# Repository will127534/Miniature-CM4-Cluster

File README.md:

# Miniature CM4 Cluster
A dense Cluster for four Raspberry Pi 4 Compute Module 4

Here is the main description: [https://will127534.github.io/Miniature-CM4-Cluster/](https://will127534.github.io/Miniature-CM4-Cluster/)

## System Arch

## Files
* ClusterHat - PCB files for CLuster Hat
* CM4Card - PCB files for CM4 Card
* Software - Code for Raspberry Pi Pico & I2C EEPROM image for USB Hub
* Mechanical - STL for the dual 4cm fan frame 

## Notes
* RTL8367N Datasheet comes from here https://github.com/libc0607/Realtek_switch_hacking
* Designed with KiCad 5.99.0-12597-g9f841da98e

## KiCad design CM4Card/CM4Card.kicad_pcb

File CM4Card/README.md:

# CM4 Card
The PCB board files for the CM4 Card

## Notes
* Because the interconnector is using M.2, the board thickness is limited to 0.8mm
* Yes, I did put most of the components under CM4. The SD card slot is 1.45mm in height. It is fine with the 3mm connector height for the CM4.
* The address for TMP117 is depend on the Cluster Hat.

## Preview

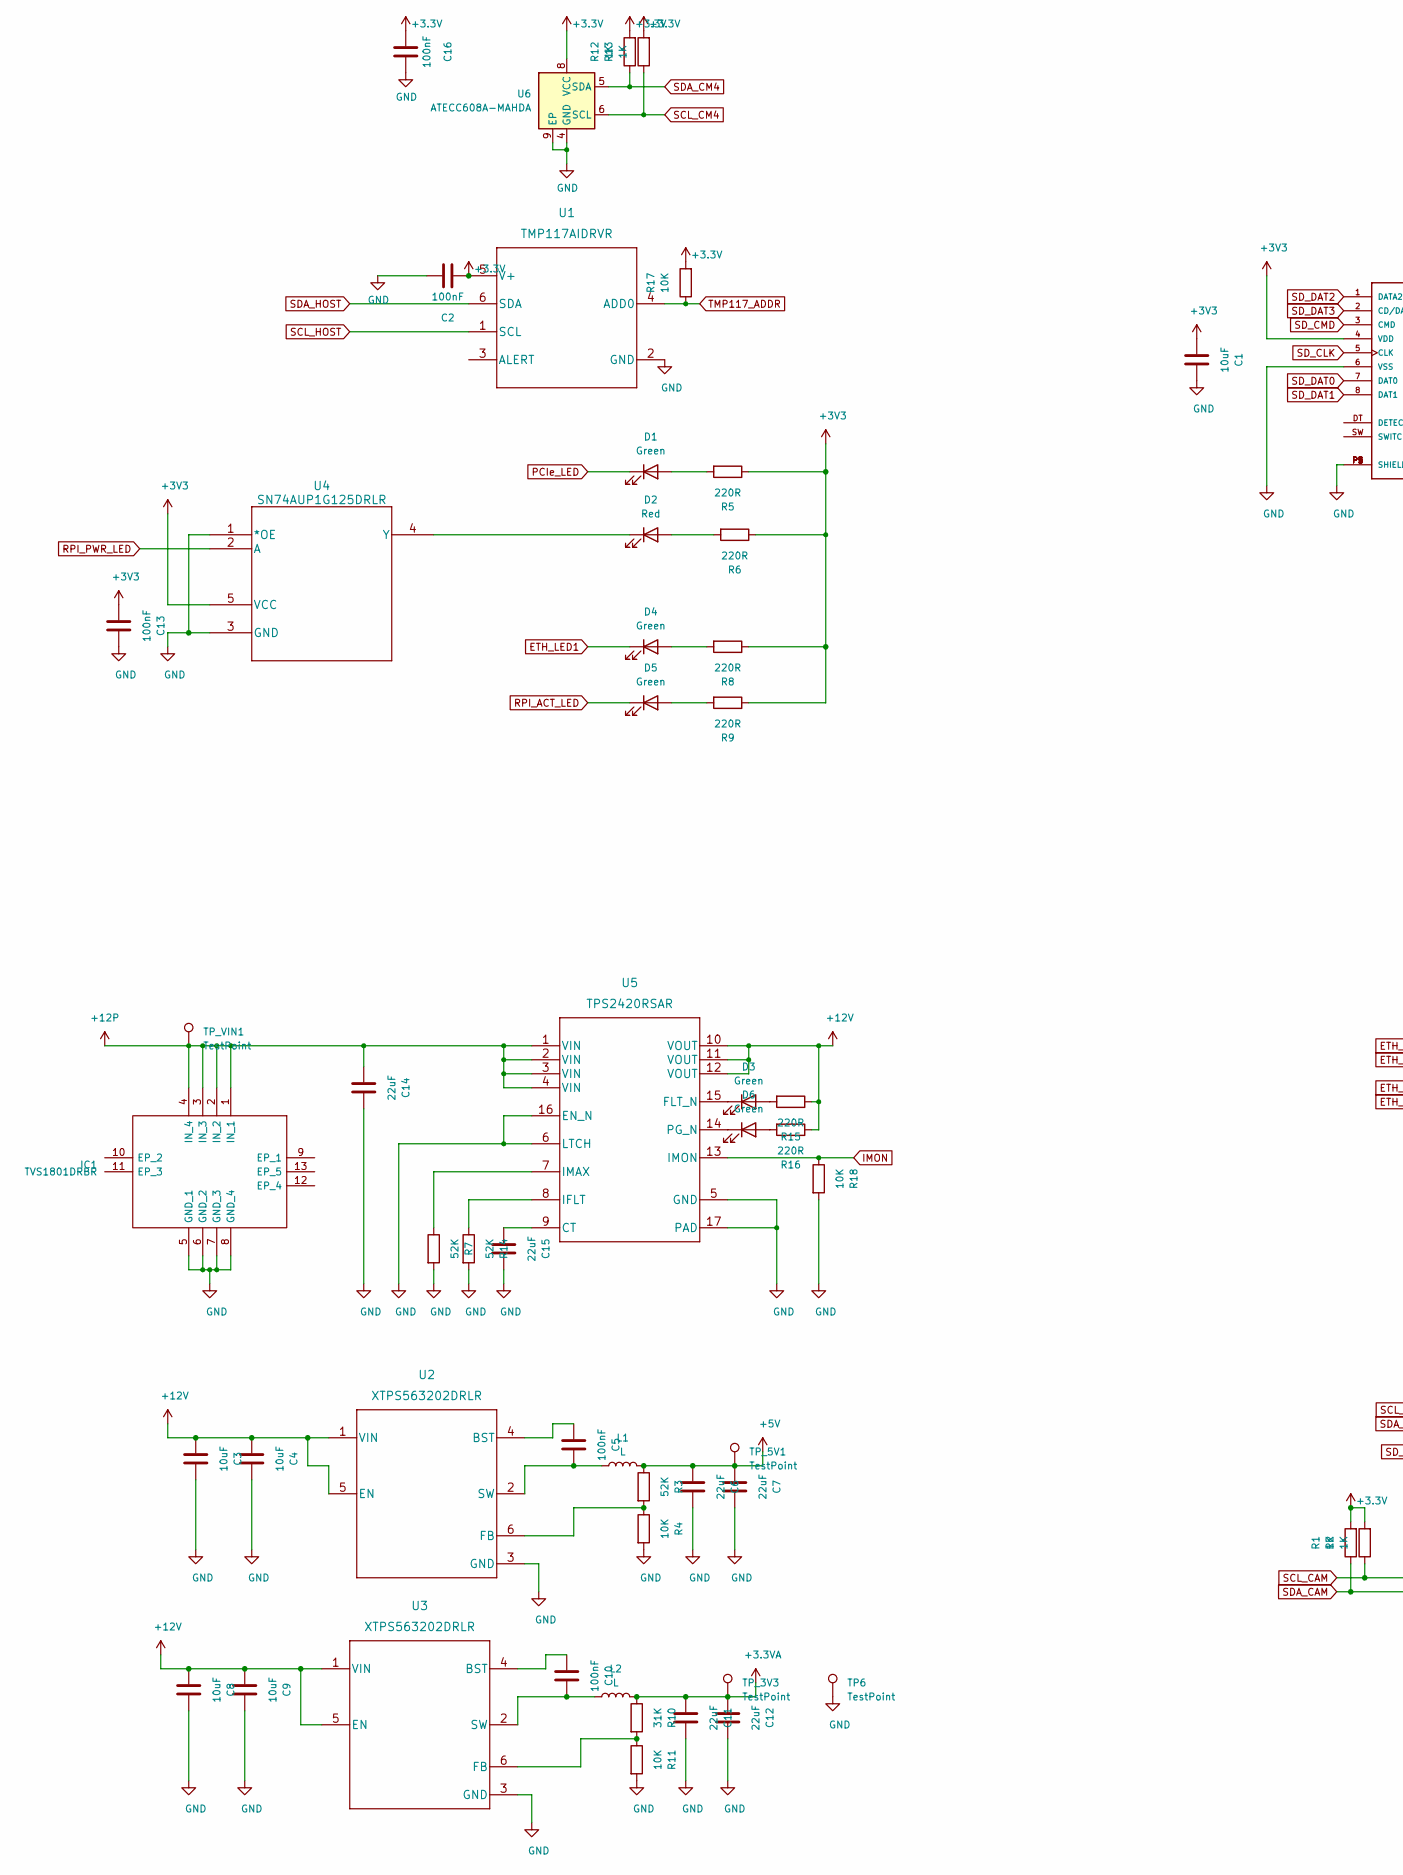
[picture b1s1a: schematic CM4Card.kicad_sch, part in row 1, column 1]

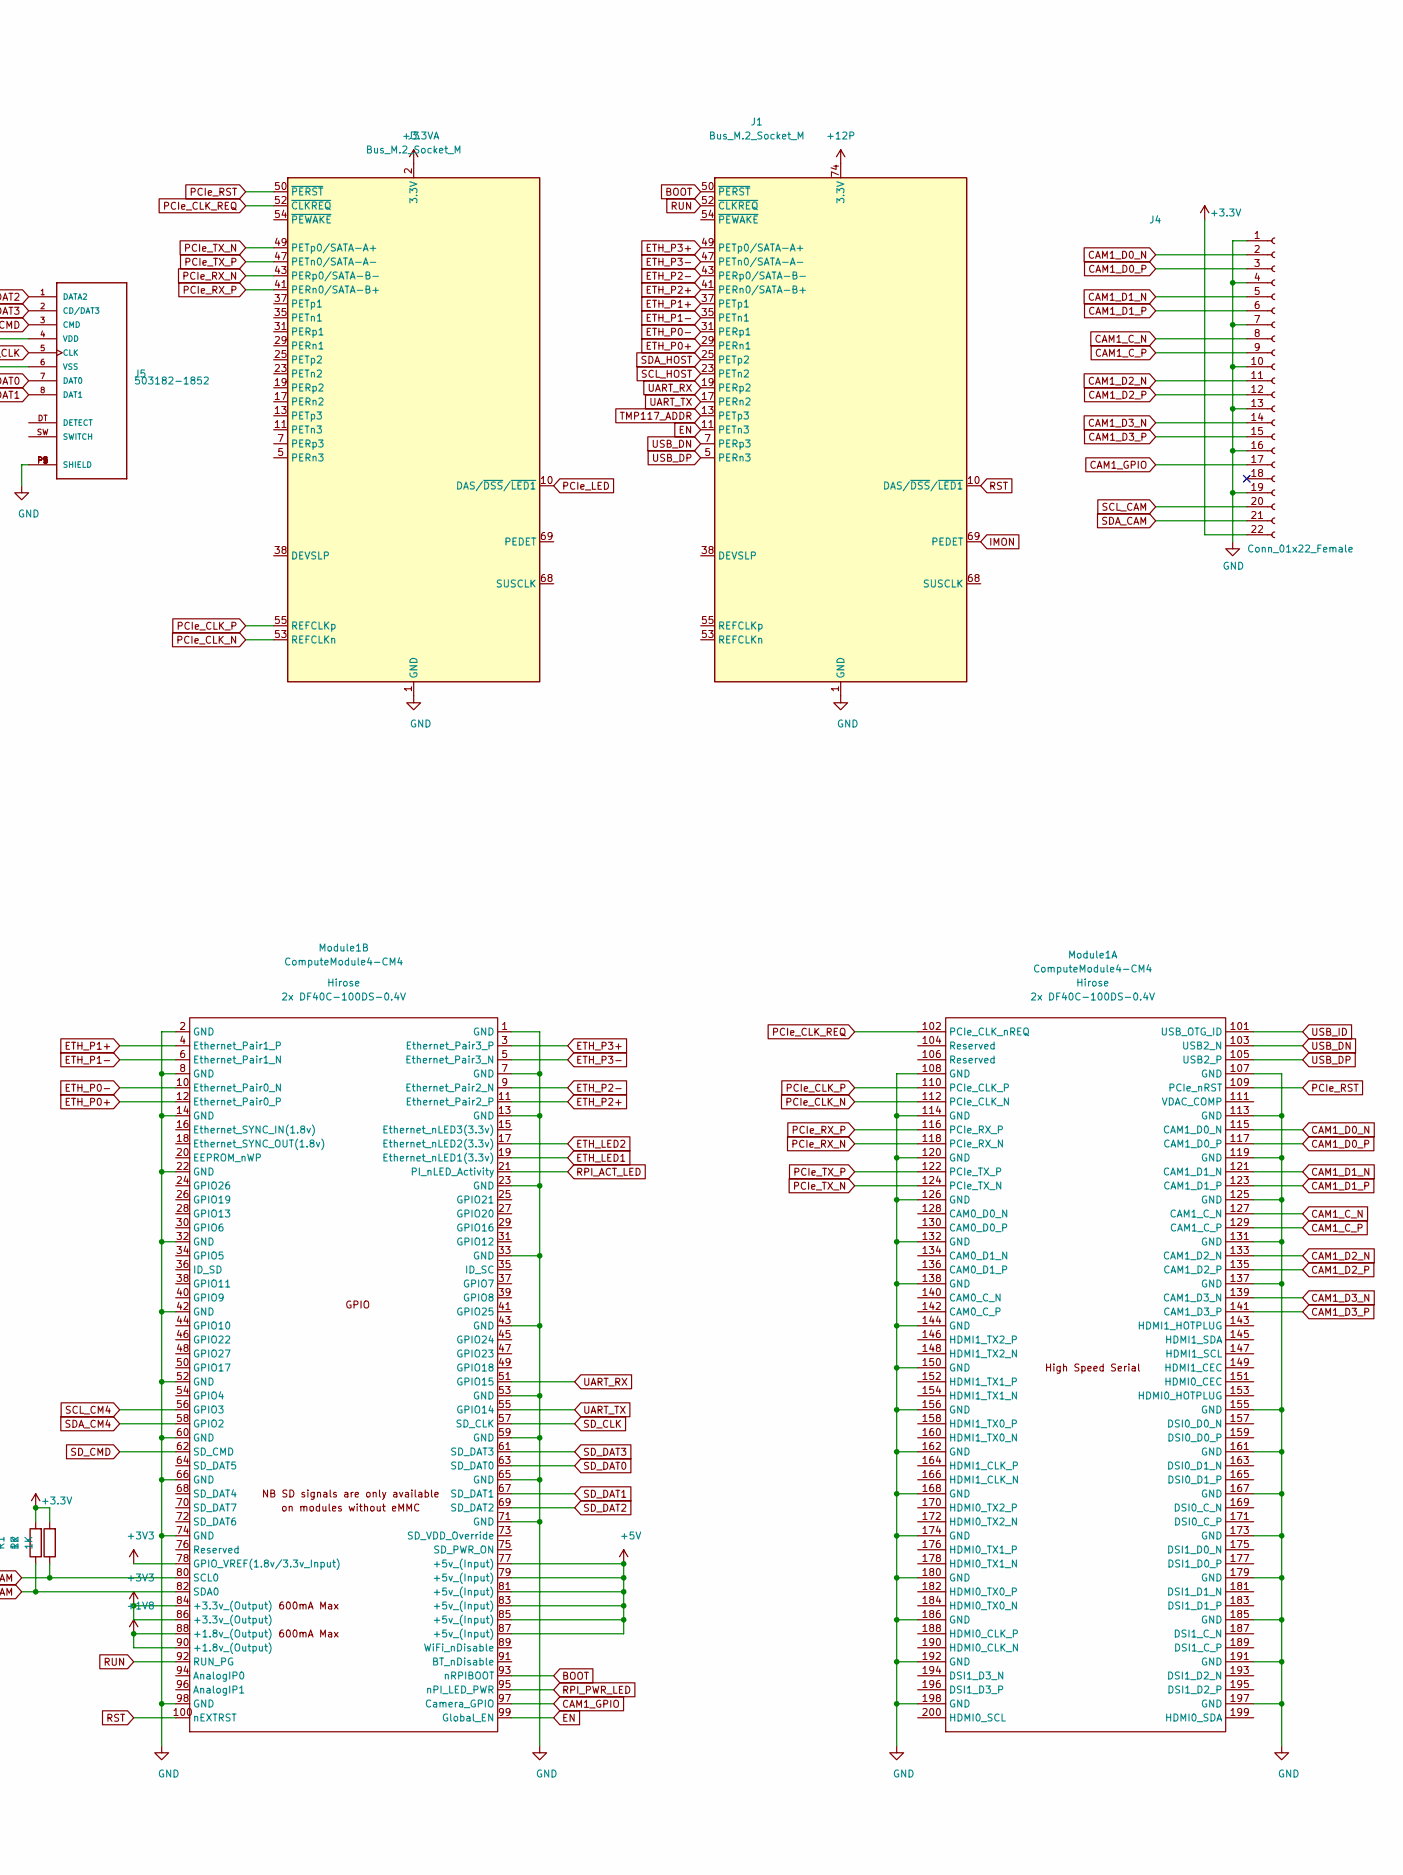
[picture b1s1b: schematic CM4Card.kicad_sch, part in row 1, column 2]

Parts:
C1, C3, C4, C8, C9: 10uF; C_0805_2012Metric
C2, C5, C10, C13, C16: 100nF; C_0402_1005Metric
C6, C7, C11, C12: 22uF; C_0805_2012Metric
C14, C15: 22uF; C_0402_1005Metric
D1, D3, D4, D5, D6: Green; LED_0603_1608Metric
D2: Red; LED_0603_1608Metric
IC1: TVS1801DRBR; TPS73601DRBR; Mouser Part Number 595-TVS1801DRBR
J1: Bus_M.2_Socket_M; NGFF_M
J3: Bus_M.2_Socket_M; 1-2199230-6
J4: Conn_01x22_Female; Hirose_FH12-22S-0.5SH_1x22-1MP_P0.50mm_Horizontal; Part Description 22 Position FFC, FPC Connector Contacts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
J5: 503182-1852; MOLEX_503182-1852
L1, L2: L; L_Coilcraft_XAL5030
Module1: ComputeModule4-CM4; Raspberry-Pi-4-Compute-Module
R1, R2, R12, R13: 1K; R_0402_1005Metric
R3, R7, R14: 52K; R_0402_1005Metric
R4, R11, R17, R18: 10K; R_0402_1005Metric
R5, R6, R8, R9, R15, R16: 220R; R_0402_1005Metric
R10: 31K; R_0402_1005Metric
TP6: TestPoint; TestPoint_Pad_D2.0mm
TP_3V3, TP_5V1: TestPoint; TestPoint_Pad_D2.0mm
TP_VIN1: TestPoint; TestPoint_Pad_D2.0mm
U1: TMP117AIDRVR
U2, U3: XTPS563202DRLR
U4: SN74AUP1G125DRLR
U5: TPS2420RSAR
U6: ATECC608A-MAHDA; DFN-8-1EP_3x2mm_P0.5mm_EP1.3x1.5mm

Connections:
+1V8: Module1.88 (+1.8v_(Output)), Module1.90 (+1.8v_(Output))
+3.3VA: C11.1, C12.1, J3.2 (3.3V), J3.4 (3.3V), J3.12 (3.3V), J3.14 (3.3V), J3.16 (3.3V), J3.18 (3.3V), J3.70 (3.3V), J3.72 (3.3V), J3.74 (3.3V), L2.2, R10.1, TP_3V3.1
+5V: C6.1, C7.1, L1.2, Module1.77 (+5v_(Input)), Module1.79 (+5v_(Input)), Module1.81 (+5v_(Input)), Module1.83 (+5v_(Input)), Module1.85 (+5v_(Input)), Module1.87 (+5v_(Input)), R3.1, TP_5V1.1
+12P: C14.1, IC1.1 (IN_1), IC1.2 (IN_2), IC1.3 (IN_3), IC1.4 (IN_4), J1.70 (3.3V), J1.72 (3.3V), J1.74 (3.3V), TP_VIN1.1, U5.1 (VIN), U5.2 (VIN), U5.3 (VIN), U5.4 (VIN)
+12V: C3.1, C4.1, C8.1, C9.1, R15.1, R16.1, U2.1 (VIN), U2.5 (EN), U3.1 (VIN), U3.5 (EN), U5.10 (VOUT), U5.11 (VOUT), U5.12 (VOUT)
BOOT: J1.50 (~PERST), Module1.93 (nRPIBOOT)
CAM1_C_N: J4.8, Module1.127 (CAM1_C_N)
CAM1_C_P: J4.9, Module1.129 (CAM1_C_P)
CAM1_D0_N: J4.2, Module1.115 (CAM1_D0_N)
CAM1_D0_P: J4.3, Module1.117 (CAM1_D0_P)
CAM1_D1_N: J4.5, Module1.121 (CAM1_D1_N)
CAM1_D1_P: J4.6, Module1.123 (CAM1_D1_P)
CAM1_D2_N: J4.11, Module1.133 (CAM1_D2_N)
CAM1_D2_P: J4.12, Module1.135 (CAM1_D2_P)
CAM1_D3_N: J4.14, Module1.139 (CAM1_D3_N)
CAM1_D3_P: J4.15, Module1.141 (CAM1_D3_P)
CAM1_GPIO: J4.17, Module1.97 (Camera_GPIO)
EN: J1.11 (PETn3), Module1.99 (Global_EN)
ETH_LED1: D4.1 (K), Module1.19 (Ethernet_nLED1(3.3v))
ETH_LED2: Module1.17 (Ethernet_nLED2(3.3v))
ETH_P0+: J1.29 (PERn1), Module1.12 (Ethernet_Pair0_P)
ETH_P0-: J1.31 (PERp1), Module1.10 (Ethernet_Pair0_N)
ETH_P1+: J1.37 (PETp1), Module1.4 (Ethernet_Pair1_P)
ETH_P1-: J1.35 (PETn1), Module1.6 (Ethernet_Pair1_N)
ETH_P2+: J1.41 (PERn0/SATA-B+), Module1.11 (Ethernet_Pair2_P)
ETH_P2-: J1.43 (PERp0/SATA-B-), Module1.9 (Ethernet_Pair2_N)
ETH_P3+: J1.49 (PETp0/SATA-A+), Module1.3 (Ethernet_Pair3_P)
ETH_P3-: J1.47 (PETn0/SATA-A-), Module1.5 (Ethernet_Pair3_N)
GND: C1.2, C2.2, C3.2, C4.2, C6.2, C7.2, C8.2, C9.2, C11.2, C12.2, C13.2, C14.2, C15.2, C16.2, IC1.5 (GND_1), IC1.6 (GND_2), IC1.7 (GND_3), IC1.8 (GND_4), J1.1 (GND), J1.3 (GND), J1.9 (GND), J1.15 (GND), J1.21 (GND), J1.27 (GND), J1.33 (GND), J1.39 (GND), J1.45 (GND), J1.51 (GND), J1.57 (GND), J1.71 (GND), J1.73 (GND), J1.75 (GND), J3.1 (GND), J3.3 (GND), J3.9 (GND), J3.15 (GND), J3.21 (GND), J3.27 (GND), J3.33 (GND), J3.39 (GND), J3.45 (GND), J3.51 (GND), J3.57 (GND), J3.71 (GND), J3.73 (GND), J3.75 (GND), J4.1, J4.4, J4.7, J4.10, J4.13, J4.16, J4.19, J5.6 (VSS), J5.P1 (SHIELD), J5.P2 (SHIELD), J5.P3 (SHIELD), J5.P4 (SHIELD), J5.P5 (SHIELD), Module1.1 (GND), Module1.2 (GND), Module1.7 (GND), Module1.8 (GND), Module1.13 (GND), Module1.14 (GND), Module1.22 (GND), Module1.23 (GND), Module1.32 (GND), Module1.33 (GND), Module1.42 (GND), Module1.43 (GND), Module1.52 (GND), Module1.53 (GND), Module1.59 (GND), Module1.60 (GND), Module1.65 (GND), Module1.66 (GND), Module1.71 (GND), Module1.74 (GND), Module1.98 (GND), Module1.107 (GND), Module1.108 (GND), Module1.113 (GND), Module1.114 (GND), Module1.119 (GND), Module1.120 (GND), Module1.125 (GND), Module1.126 (GND), Module1.131 (GND), Module1.132 (GND), Module1.137 (GND), Module1.138 (GND), Module1.144 (GND), Module1.150 (GND), Module1.155 (GND), Module1.156 (GND), Module1.161 (GND), Module1.162 (GND), Module1.167 (GND), Module1.168 (GND), Module1.173 (GND), Module1.174 (GND), Module1.179 (GND), Module1.180 (GND), Module1.185 (GND), Module1.186 (GND), Module1.191 (GND), Module1.192 (GND), Module1.197 (GND), Module1.198 (GND), R4.2, R7.2, R11.2, R14.2, R18.2, TP6.1, U1.2 (GND), U2.3 (GND), U3.3 (GND), U4.1 (*OE), U4.3 (GND), U5.5 (GND), U5.6 (LTCH), U5.16 (EN_N), U5.17 (PAD), U6.4 (GND), U6.9 (EP)
IMON: J1.69 (PEDET), R18.1, U5.13 (IMON)
unnamed: C5.1, U2.4 (BST)
unnamed: C5.2, L1.1, U2.2 (SW)
unnamed: C10.1, U3.4 (BST)
unnamed: C10.2, L2.1, U3.2 (SW)
unnamed: C15.1, U5.9 (CT)
unnamed: D1.2 (A), R5.2
unnamed: D2.1 (K), U4.4 (Y)
unnamed: D2.2 (A), R6.2
unnamed: D3.1 (K), U5.15 (FLT_N)
unnamed: D3.2 (A), R15.2
unnamed: D4.2 (A), R8.2
unnamed: D5.2 (A), R9.2
unnamed: D6.1 (K), U5.14 (PG_N)
unnamed: D6.2 (A), R16.2
unnamed: R3.2, R4.1, U2.6 (FB)
unnamed: R7.1, U5.7 (IMAX)
unnamed: R10.2, R11.1, U3.6 (FB)
unnamed: R14.1, U5.8 (IFLT)
PCIe_CLK_N: J3.53 (REFCLKn), Module1.112 (PCIe_CLK_N)
PCIe_CLK_P: J3.55 (REFCLKp), Module1.110 (PCIe_CLK_P)
PCIe_CLK_REQ: J3.52 (~CLKREQ), Module1.102 (PCIe_CLK_nREQ)
PCIe_LED: D1.1 (K), J3.10 (DAS/~DSS/~LED1)
PCIe_RST: J3.50 (~PERST), Module1.109 (PCIe_nRST)
PCIe_RX_N: J3.43 (PERp0/SATA-B-), Module1.118 (PCIe_RX_N)
PCIe_RX_P: J3.41 (PERn0/SATA-B+), Module1.116 (PCIe_RX_P)
PCIe_TX_N: J3.49 (PETp0/SATA-A+), Module1.124 (PCIe_TX_N)
PCIe_TX_P: J3.47 (PETn0/SATA-A-), Module1.122 (PCIe_TX_P)
RPI_ACT_LED: D5.1 (K), Module1.21 (PI_nLED_Activity)
RPI_PWR_LED: Module1.95 (nPI_LED_PWR), U4.2 (A)
RST: J1.10 (DAS/~DSS/~LED1), Module1.100 (nEXTRST)
RUN: J1.52 (~CLKREQ), Module1.92 (RUN_PG)
SCL_CAM: J4.20, Module1.80 (SCL0), R2.1
SCL_CM4: Module1.56 (GPIO3), R13.1, U6.6 (SCL)
SCL_HOST: J1.23 (PETn2), U1.1 (SCL)
SDA_CAM: J4.21, Module1.82 (SDA0), R1.1
SDA_CM4: Module1.58 (GPIO2), R12.1, U6.5 (SDA)
SDA_HOST: J1.25 (PETp2), U1.6 (SDA)
SD_CLK: J5.5 (CLK), Module1.57 (SD_CLK)
SD_CMD: J5.3 (CMD), Module1.62 (SD_CMD)
SD_DAT0: J5.7 (DAT0), Module1.63 (SD_DAT0)
SD_DAT1: J5.8 (DAT1), Module1.67 (SD_DAT1)
SD_DAT2: J5.1 (DATA2), Module1.69 (SD_DAT2)
SD_DAT3: J5.2 (CD/DAT3), Module1.61 (SD_DAT3)
TMP117_ADDR: J1.13 (PETp3), R17.1, U1.4 (ADD0)
UART_RX: J1.19 (PERp2), Module1.51 (GPIO15)
UART_TX: J1.17 (PERn2), Module1.55 (GPIO14)
USB_DN: J1.7 (PERp3), Module1.103 (USB2_N)
USB_DP: J1.5 (PERn3), Module1.105 (USB2_P)
USB_ID: Module1.101 (USB_OTG_ID)

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
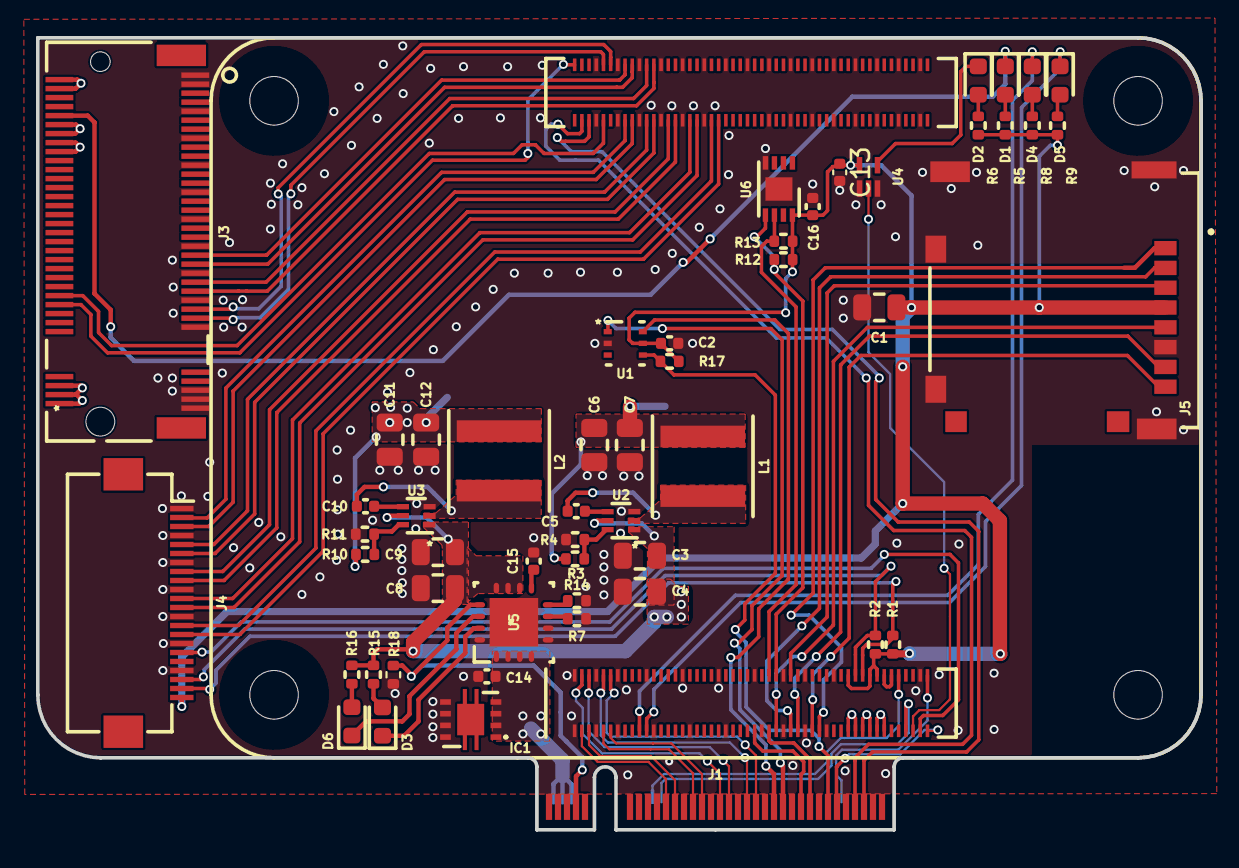
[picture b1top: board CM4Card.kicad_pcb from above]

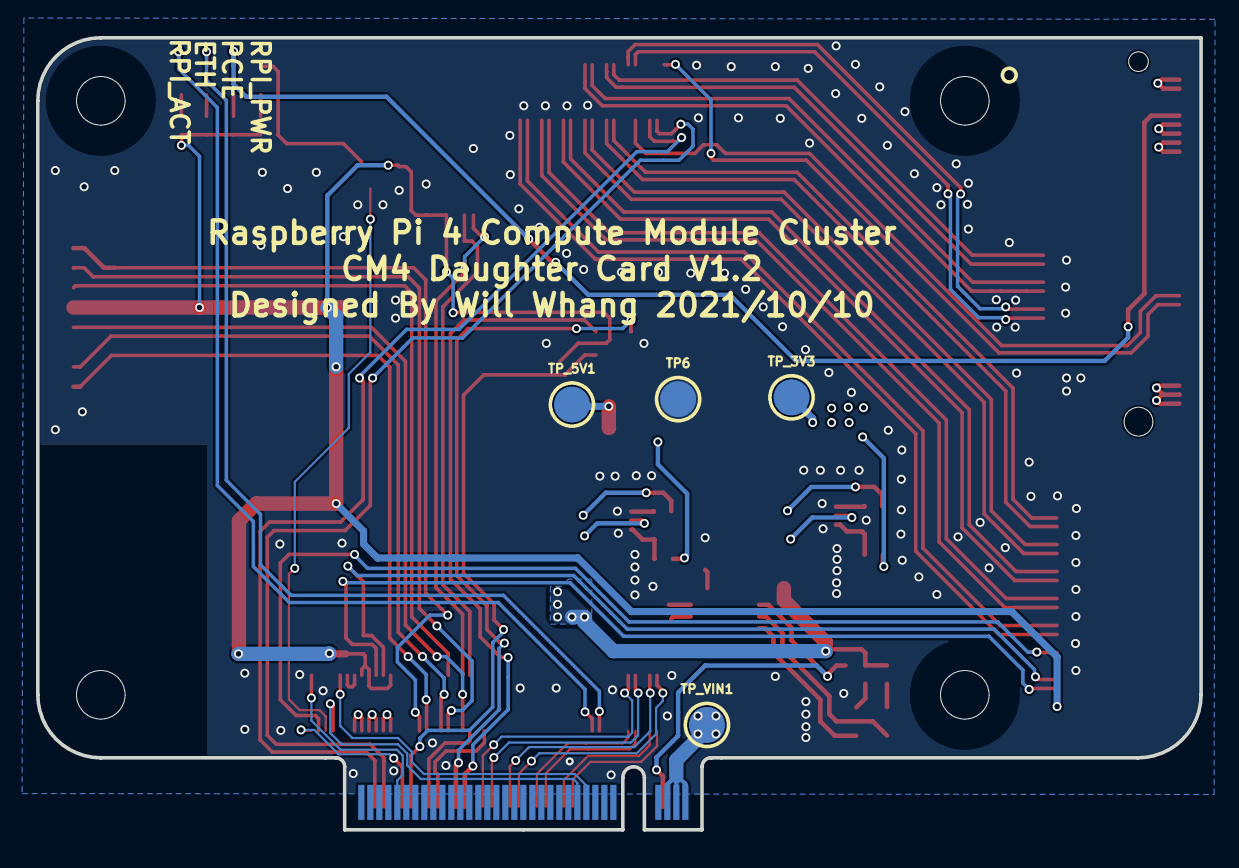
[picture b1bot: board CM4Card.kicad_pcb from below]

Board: 4 copper layers, 64.6 x 44.0 mm, 58 parts (4 on the bottom side), 78 nets.

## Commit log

2021-11-23 Set theme jekyll-theme-midnight
2021-11-26 initial
2021-11-26 Comment from test on
2021-11-26 Comment from test on index
2021-11-28 initialize commit
2021-11-28 Adding github page
2022-01-05 Comment from will on index
2022-01-05 remove .DS_store

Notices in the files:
parts and their libraries:
Copyright 2021 Accelerated Designs. All rights reserved.
